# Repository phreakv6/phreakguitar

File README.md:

# PhreakGuitar

A guitar rig in your browser, built on circuit simulation. Plug in an audio
interface and play through amps and pedals whose analog circuits are solved
in real time: every resistor, capacitor, diode, transistor and tube, the same
netlists a SPICE simulator runs, checked against ngspice.

**Live:** https://phreakguitar.com

## What's in it

- **11 amps** as circuit models: tweed, black-panel, British plexi and
  master-volume, class A, high-headroom, graphic-panel, boutique overdrive
  (plus an experimental hot-rod high-gain head). Each has its own power
  section with a simulated power supply that sags and recovers, a Response
  knob, and a glowing tube view.
- **12 pedals**: wah, clean and treble boosters, silicon and germanium
  round fuzz, octave fuzz, two overdrives, a distortion, a four-stage
  phaser (with its LFO in the circuit), a photocell vibe (a measured DSP
  model, the one pedal that isn't a solved circuit) and a four-stage
  fuzz; plus a compressor, 7-band EQ, digital delay, reverb and a looper.
- **Song tones and factory presets**, level-matched, with notes on how to
  play them; save, compare (A/B), export and import your own.
- **Pedal designer**: fork any pedal, swap parts and models, add parts on the
  schematic, probe any point with a live scope, hear each change as you play.
- **Tabs beside the rig**: open Guitar Pro or MusicXML files, play along
  with a cursor, slow it down, loop a section, mute your part.
- **Stage view**, keyboard shortcuts, a tuner, cab IRs (built-in or your
  own WAV files), and a latency readout with a loopback measurement.

## Using it

- Use an audio interface and headphones or speakers. A laptop's built-in
  microphone and speakers will feed back.
- Chrome or Edge on a desktop is best (they let you pick the output
  device). Safari and Firefox mostly work.
- Your audio never leaves your computer: everything runs in the browser, and
  presets, IRs and tabs are stored in it. The public site counts anonymous
  usage (page views, power on/off, which amps, pedals and presets get picked)
  with PostHog: no cookies, no recordings, no file names. Add `?notrack` to
  the address to opt out; builds you run yourself send nothing.
- Add `?rename` to the address to give the amps and pedals your own names
  (a Rename button by the amp and on the open pedal circuit). They're kept
  in your browser only; a blank name restores the built-in one.

## Running it locally

You need [Node.js](https://nodejs.org) 20+ and
[Emscripten](https://emscripten.org/docs/getting_started/downloads.html)
(installed to `~/emsdk`, or with `em++` on your `PATH`).

```sh
cd web
npm install
npm run dev        # builds the engine to WebAssembly, then serves the app
```

Open the printed URL (http://localhost:5173). The dev server also lists
cab IRs from `~/Music/PhreakGuitar/IRs` and tab files from
`~/Music/PhreakGuitar/Tabs` and `~/Downloads`.

The native build (unit tests, the offline render tool, a JUCE plugin) uses
CMake 3.24+ and a C++20 compiler; it fetches JUCE and Catch2:

```sh
cmake -B build -DCMAKE_BUILD_TYPE=Release
cmake --build build --config Release
ctest --test-dir build -C Release
tools/run_checks.sh   # the full suite; circuit checks need ngspice
```

## How it works

See [docs/ARCHITECTURE.md](docs/ARCHITECTURE.md): the nodal DK-method
solver, circuits as SPICE files, amps and power supplies, the browser
engine. What's next: [docs/ROADMAP.md](docs/ROADMAP.md).

## License

GPLv3, see [LICENSE](LICENSE). Third-party components and their licenses:
[THIRD_PARTY_NOTICES.md](THIRD_PARTY_NOTICES.md).

Amp and pedal models are named for the kind of gear they are, and each says
which original it's based on. Those product names (in the app and in source
comments) are trademarks of their owners, used only to identify the circuits
a model studies. PhreakGuitar is
not affiliated with or endorsed by any manufacturer.

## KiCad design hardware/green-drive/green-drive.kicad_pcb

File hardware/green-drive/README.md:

# Green Drive: the real pedal

The '808-style overdrive from `pedals/green-drive.cir`, as a board you can
order, solder and put in a 3D-printed box. The board's audio circuit is the
one the app plays, part for part: `check.py` compares KiCad's netlist with the
`.cir` on every build.

## What's here

| File | What it is |
|---|---|
| `out/green-drive-gerbers.zip` | **Upload this to Lion Circuits.** 2 layers, 64 x 66 mm |
| `out/assembly.pdf` | Soldering map: every part with its value, polarity marked |
| `out/bom.csv` | Parts list |
| `out/case_shell.stl`, `out/case_bottom.stl` | The box (print after measuring your parts, below) |
| `out/green-drive-schematic.pdf` | The schematic |
| `green-drive.kicad_pro` / `_sch` / `_pcb` | The KiCad project, if you want to change anything |
| `design.py` | Every part and what it connects to: the source of the rest |

## 1. Order the board

[lioncircuits.com](https://www.lioncircuits.com) → instant quote → upload
`out/green-drive-gerbers.zip`. Defaults are fine: 2 layers, FR-4 1.6 mm,
HASL, green mask, white legend, quantity 5. About ₹799, 5 to 6 days.

## 2. Buy the parts (Robu.in, checked 10 Nov 2026)

| Qty | Part | Value | On the board |
|---|---|---|---|
| 1 | Resistor 1/4 W metal film | 100 | R14 |
| 1 | Resistor 1/4 W metal film | 220 | R9 |
| 4 | Resistor 1/4 W metal film | 1k | R1, R7, R8, R10 |
| 1 | Resistor 1/4 W metal film | 2.2k | R21 |
| 1 | Resistor 1/4 W metal film | 4.7k | R6 |
| 7 | Resistor 1/4 W metal film | 10k | R3, R4, R13, R15, R16, R17, R18 |
| 1 | Resistor 1/4 W metal film | 15k | R20 |
| 1 | Resistor 1/4 W metal film | 51k | R5 |
| 1 | Resistor 1/4 W metal film | 510k | R2 |
| 2 | Resistor 1/4 W metal film | 1M | R12, R19 |
| 1 | Film capacitor | 22n | C1 |
| 1 | Film capacitor | 47n | C3 |
| 1 | Film capacitor | 100n | C7 |
| 2 | Film capacitor | 220n | C6, C10 |
| 1 | Ceramic capacitor | 47p | C11 |
| 1 | Ceramic capacitor | 100n | C13 |
| 2 | Electrolytic capacitor, 25 V+ | 1u | C2, C5 |
| 1 | Electrolytic capacitor, 25 V+ | 10u | C8 |
| 1 | Electrolytic capacitor, 25 V+ | 47u | C9 |
| 1 | Electrolytic capacitor, 25 V+ | 100u | C12 |
| 2 | Diode | 1N4148 | D1, D3 |
| 1 | Schottky diode | 1N5819 | D4 |
| 2 | NPN transistor | 2SC1815 | Q1, Q2 |
| 1 | Dual op-amp, DIP-8 | JRC4558D (also try RC4558P, TL072) | U1 |
| 1 | Pot, 16 mm, PCB legs | B500K (A500K if you find one) | RV1 Drive |
| 1 | Pot, 16 mm, PCB legs | B20K | RV2 Tone |
| 1 | Pot, 16 mm, PCB legs | B100K (A100K if you find one) | RV3 Level |
| 1 | LED, 5 mm | red | LED1 |
| 1 | 8-pin DIP socket | | U1 |
| 1 | 3PDT footswitch | Daier PBS-24-302P | |
| 2 | 1/4" jack | CK-6.35-03 (stereo is fine) | |
| 1 | DC jack, panel mount | 2.1 x 5.5 mm | |
| 3 | Knob, 6 mm shaft | | |
| 4 | M3 x 5 mm brass heat-set insert + M3 x 6 mm countersunk screw | | bottom plate |
| | 24 AWG wire, two colours | | |

Notes:
- The board takes film caps at **5 mm or 10 mm** lead spacing (three holes:
  use the pair that fits) and the 47p at 2.5 or 5 mm.
- **R20 (15k)** makes the linear Level pot feel like an audio-taper one. With
  an A100K pot, leave R20 out.
- C1 is 22n (the original's 20n is rare) and C11 47p (51p): both checked in
  ngspice, under 0.5 dB anywhere on the knobs.

## 3. Solder

Follow `out/assembly.pdf`. Low parts first, so the board lies flat while you
work:

1. Resistors, the three diodes (band = **K** on the map)
2. The DIP socket (notch at the **1** end), the 47p and 100n ceramics
3. The transistors: the **thick line on the map is the flat face**, legs E-C-B
4. Film caps, then electrolytics (long leg = **+**)
5. Wires to the pads: about 10 cm each, two colours for 9V and GND
6. **Last, on the other side of the board:** the pots and the LED. Push the
   pots' shafts through the printed lid first and screw the nuts on, then
   solder, so they line up with the holes. Push the LED until its tip sits in
   the lid's LED hole, then solder it. Break off the pots' little
   anti-rotation tabs with pliers.

Don't put the op-amp in yet.

## 4. Test before boxing

9 V adapter on the 9V and GND pads, multimeter on DC volts, black probe on
GND. Without the op-amp:

| Where | Expect |
|---|---|
| D4's band end (VCC) | 8.5 to 8.8 V (the diode takes 0.3 to 0.4 V) |
| C9's + leg (VREF) | half of that, about 4.3 V |

Then power off, put the op-amp in (notch to the **1** end), power on:

| Where | Expect (from ngspice, scaled to the real supply) |
|---|---|
| U1 pins 1, 2, 3, 5, 6, 7 | all about VREF (4.3 V) |
| Q1 emitter (E) | about 3.1 V |
| Q2 emitter (E) | about 2.7 V |

The pedal should draw about 10 mA with the LED on. If it draws much more
than 20 mA, or a voltage is way off, power off
and look for a solder bridge or a part in backwards before going further.

## 5. Wire the jacks and footswitch

Check the footswitch with a multimeter on continuity first: its 9 lugs are
three columns of three. In each column the middle lug connects to the top lug
in one position and to the bottom lug in the other. Looking at the lugs:

```
 1  2  3     top row:    bypass
 4  5  6     middle row: commons
 7  8  9     bottom row: effect on
```

| From | To |
|---|---|
| Lug 4 | Output jack tip |
| Lug 5 | Input jack tip |
| Lug 6 | GND |
| Lug 1 | Lug 2 (a short jumper: the bypass path) |
| Lug 7 | Board **OUT** pad |
| Lug 8 | Board **IN** pad |
| Lug 9 | Board **LED-** pad |
| Both jack sleeves | Board **GND** pad (the one next to IN) |
| DC jack centre pin | Board **GND** pad (the one next to 9V) |
| DC jack sleeve | Board **9V** pad |

Use the stereo jacks' tip and sleeve only; leave the ring lug empty. Find the
DC jack's centre-pin lug with the multimeter. Pedal adapters are centre
negative; if one is wired backwards, D4 blocks it and nothing is harmed.

If the LED lights when the pedal is bypassed, the rows are the other way up
on your switch: swap the top-row and bottom-row wires.

## 6. The box

`out/case_shell.stl` (print it lid-down: no supports, flat face) and
`out/case_bottom.stl`. PETG or PLA, 4 walls, 40% infill.

**Before printing, measure your parts** and set the values marked MEASURE in
`enclosure.py`, then run `python3 enclosure.py`:
- the pot bushing, jack and DC jack threads (hole sizes)
- `POT_SHAFT_OFFSET_MEASURED`: shaft centre to the row of pins on your pots
  (the board assumes 7.5 mm). Only the lid's holes move; the board stays as
  ordered.

Press the M3 inserts into the four corner posts with a soldering iron. The
input jack goes on the right side as you look at the knobs, output and DC
jack on the left.

## 7. Rebuilding after a change

```
python3 build.py      # schematic, netlist, ERC, check against the .cir
KPY=/Applications/KiCad/KiCad.app/Contents/Frameworks/Python.framework/Versions/3.9/bin/python3.9
$KPY pcb.py           # place the parts
$KPY route.py path/to/freerouting.jar   # route (Freerouting 2.5, needs Java)
kicad-cli pcb drc --schematic-parity --refill-zones green-drive.kicad_pcb
python3 assembly.py && python3 bom.py && python3 enclosure.py
./fab.sh              # Gerbers + drill -> out/green-drive-gerbers.zip
```
Freerouting is at github.com/freerouting/freerouting/releases.

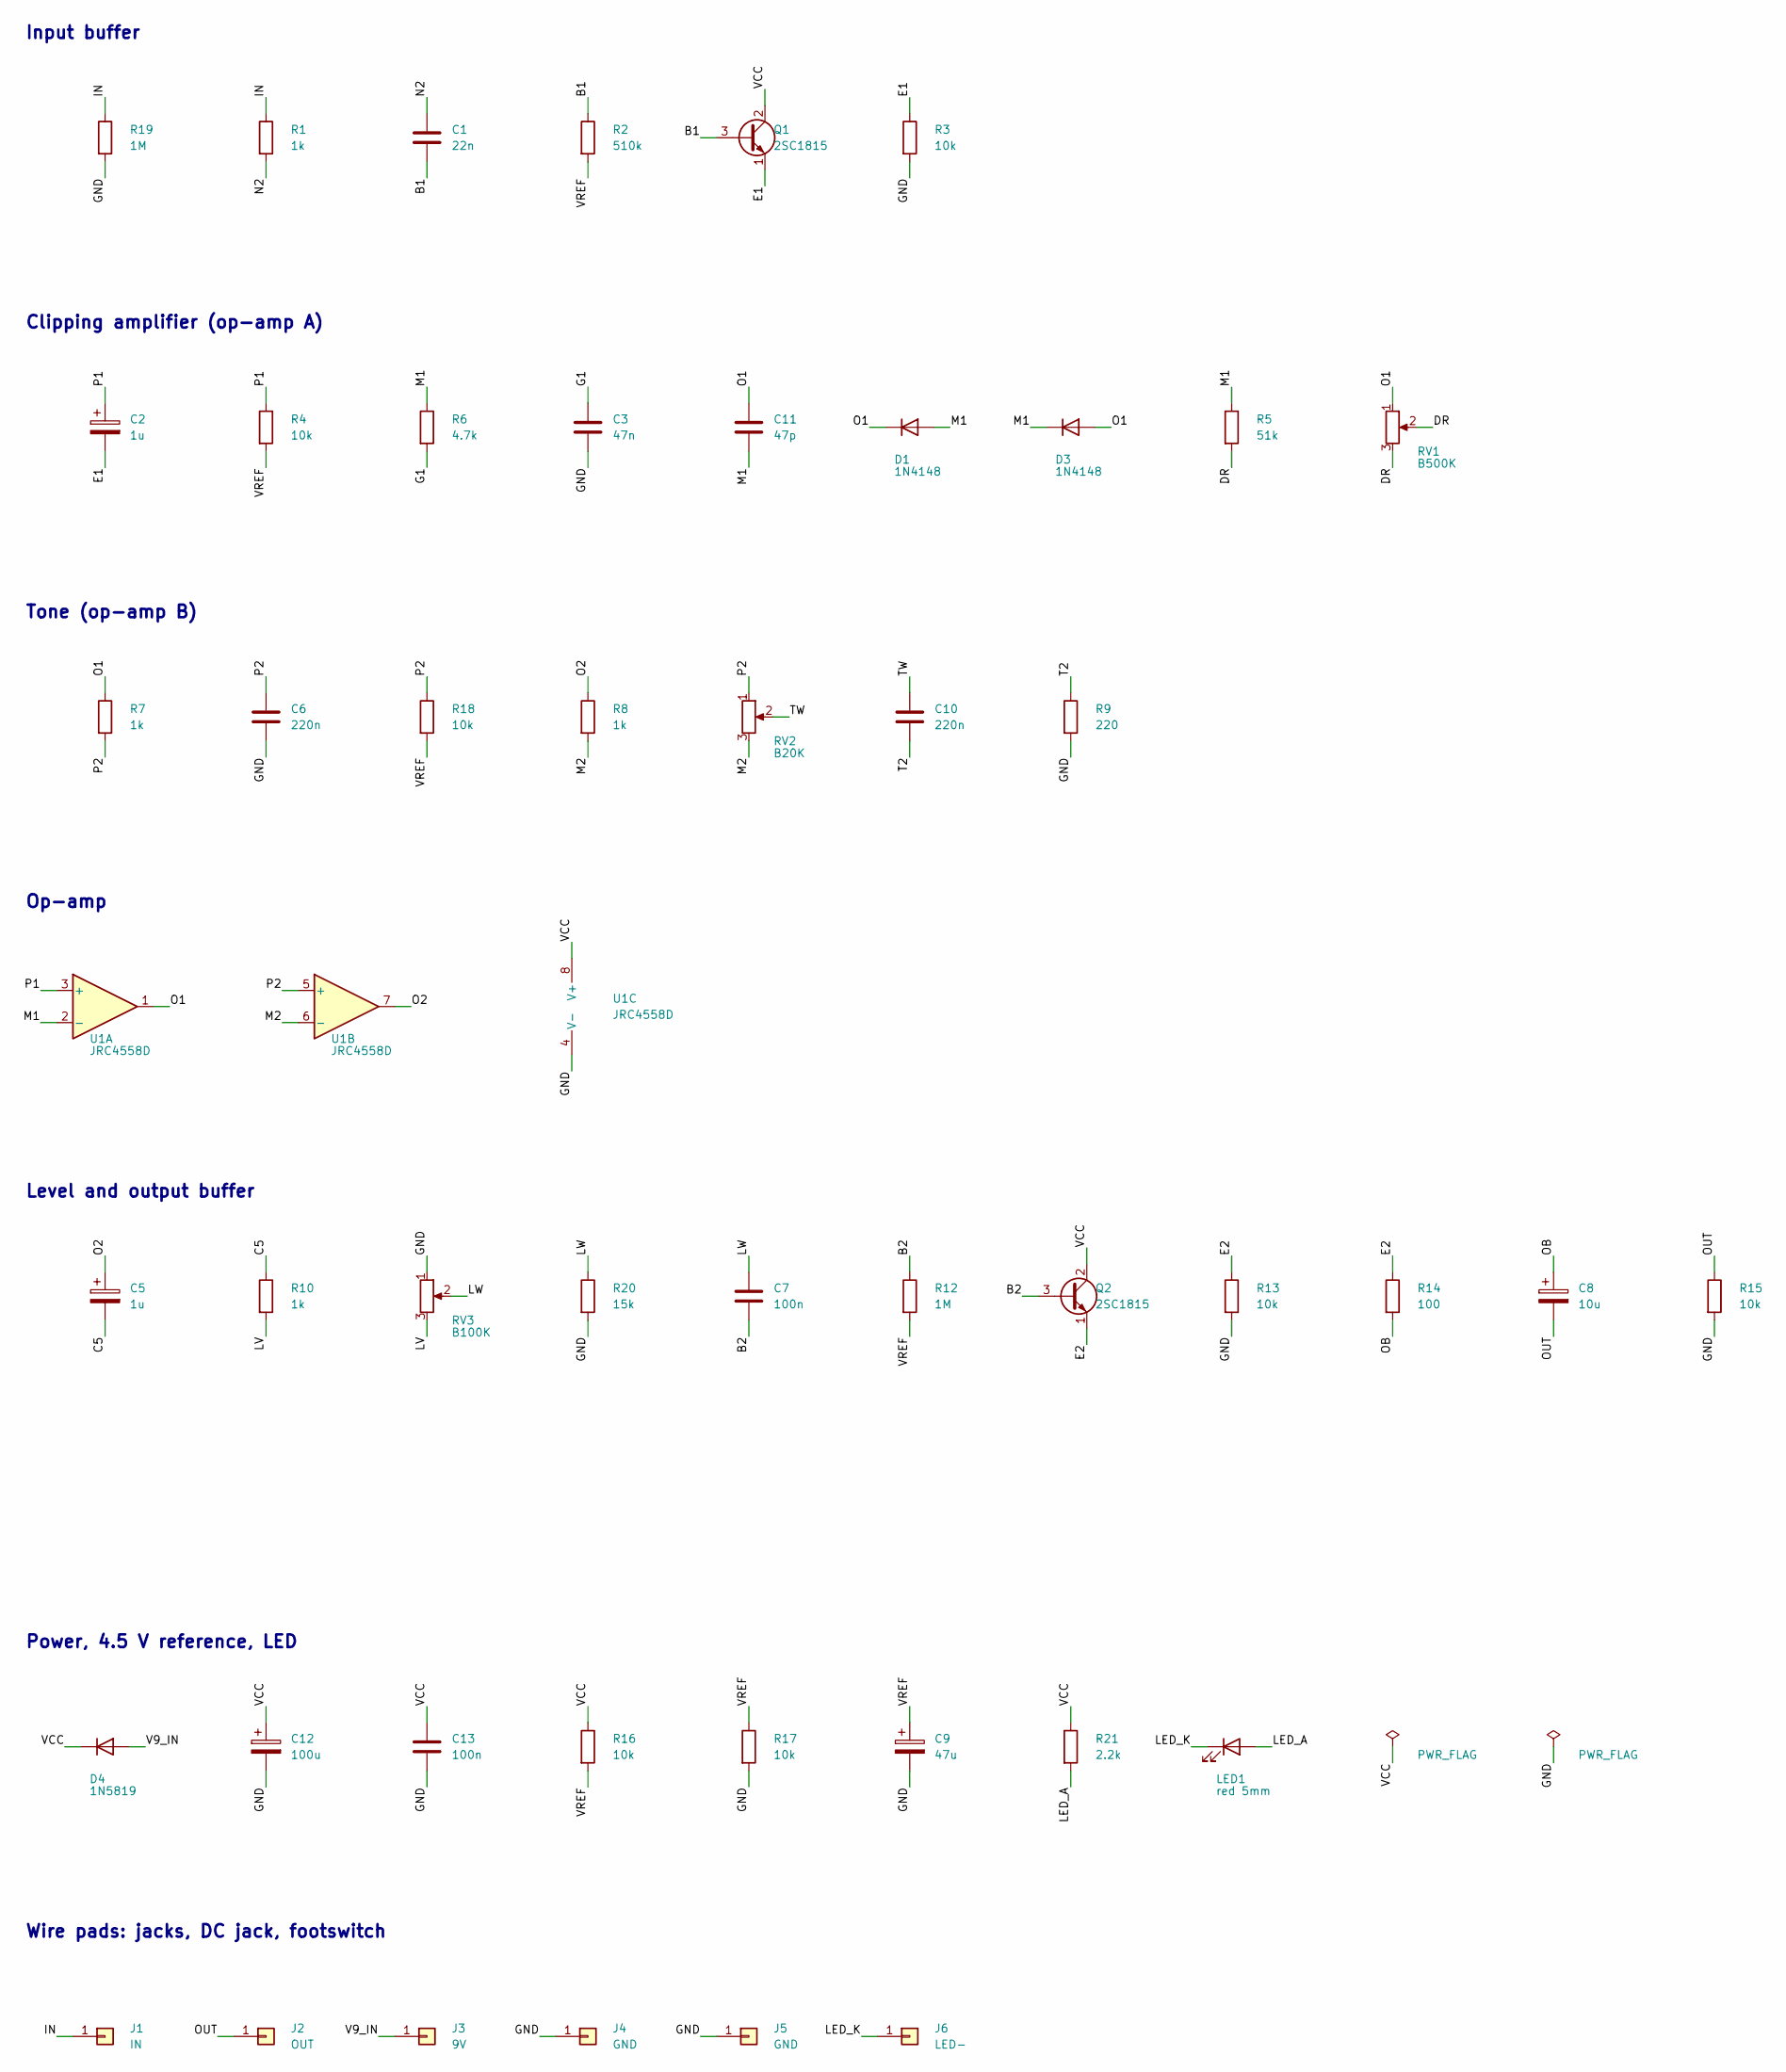
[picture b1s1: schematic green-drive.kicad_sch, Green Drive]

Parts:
C1: 22n; C_Film_P5_P10
C2, C5: 1u; CP_Radial_D5.0mm_P2.00mm
C3: 47n; C_Film_P5_P10
C6, C10: 220n; C_Film_P5_P10
C7: 100n; C_Film_P5_P10
C8: 10u; CP_Radial_D5.0mm_P2.00mm
C9: 47u; CP_Radial_D5.0mm_P2.00mm
C11: 47p; C_Disc_P2.5_P5
C12: 100u; CP_Radial_D6.3mm_P2.50mm
C13: 100n; C_Disc_P2.5_P5
D1, D3: 1N4148; D_DO-35_SOD27_P7.62mm_Horizontal
D4: 1N5819; D_DO-41_SOD81_P10.16mm_Horizontal
J1: IN; SolderWire-0.5sqmm_1x01_D0.9mm_OD2.1mm
J2: OUT; SolderWire-0.5sqmm_1x01_D0.9mm_OD2.1mm
J3: 9V; SolderWire-0.5sqmm_1x01_D0.9mm_OD2.1mm
J4, J5: GND; SolderWire-0.5sqmm_1x01_D0.9mm_OD2.1mm
J6: LED-; SolderWire-0.5sqmm_1x01_D0.9mm_OD2.1mm
LED1: red 5mm; LED_D5.0mm
Q1, Q2: 2SC1815; TO-92_Inline
R1, R7, R8, R10: 1k; R_Axial_DIN0207_L6.3mm_D2.5mm_P7.62mm_Horizontal
R2: 510k; R_Axial_DIN0207_L6.3mm_D2.5mm_P7.62mm_Horizontal
R3, R4, R13, R15, R16, R17, R18: 10k; R_Axial_DIN0207_L6.3mm_D2.5mm_P7.62mm_Horizontal
R5: 51k; R_Axial_DIN0207_L6.3mm_D2.5mm_P7.62mm_Horizontal
R6: 4.7k; R_Axial_DIN0207_L6.3mm_D2.5mm_P7.62mm_Horizontal
R9: 220; R_Axial_DIN0207_L6.3mm_D2.5mm_P7.62mm_Horizontal
R12, R19: 1M; R_Axial_DIN0207_L6.3mm_D2.5mm_P7.62mm_Horizontal
R14: 100; R_Axial_DIN0207_L6.3mm_D2.5mm_P7.62mm_Horizontal
R20: 15k; R_Axial_DIN0207_L6.3mm_D2.5mm_P7.62mm_Horizontal
R21: 2.2k; R_Axial_DIN0207_L6.3mm_D2.5mm_P7.62mm_Horizontal
RV1: B500K; Pot_WH148_16mm
RV2: B20K; Pot_WH148_16mm
RV3: B100K; Pot_WH148_16mm
U1: JRC4558D; DIP-8_W7.62mm_Socket

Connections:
/B1: C1.2, Q1.3 (B), R2.1
/B2: C7.2, Q2.3 (B), R12.1
/C5: C5.2, R10.1
/DR: R5.2, RV1.2, RV1.3
/E1: C2.2, Q1.1 (E), R3.1
/E2: Q2.1 (E), R13.1, R14.1
/G1: C3.1, R6.2
/GND: C3.2, C6.2, C9.2, C12.2, C13.2, J4.1, J5.1, R3.2, R9.2, R13.2, R15.2, R17.2, R19.2, R20.2, RV3.1, U1.4 (V-)
/IN: J1.1, R1.1, R19.1
/LED_A: LED1.2 (A), R21.2
/LED_K: J6.1, LED1.1 (K)
/LV: R10.2, RV3.3
/LW: C7.1, R20.1, RV3.2
/M1: C11.2, D1.2 (A), D3.1 (K), R5.1, R6.1, U1.2 (-)
/M2: R8.2, RV2.3, U1.6 (-)
/N2: C1.1, R1.2
/O1: C11.1, D1.1 (K), D3.2 (A), R7.1, RV1.1, U1.1
/O2: C5.1, R8.1, U1.7
/OB: C8.1, R14.2
/OUT: C8.2, J2.1, R15.1
/P1: C2.1, R4.1, U1.3 (+)
/P2: C6.1, R7.2, R18.1, RV2.1, U1.5 (+)
/T2: C10.2, R9.1
/TW: C10.1, RV2.2
/V9_IN: D4.2 (A), J3.1
/VCC: C12.1, C13.1, D4.1 (K), Q1.2 (C), Q2.2 (C), R16.1, R21.1, U1.8 (V+)
/VREF: C9.1, R2.2, R4.2, R12.2, R16.2, R17.1, R18.2

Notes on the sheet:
Input buffer
Clipping amplifier (op-amp A)
Tone (op-amp B)
Op-amp
Level and output buffer
Power, 4.5 V reference, LED
Wire pads: jacks, DC jack, footswitch

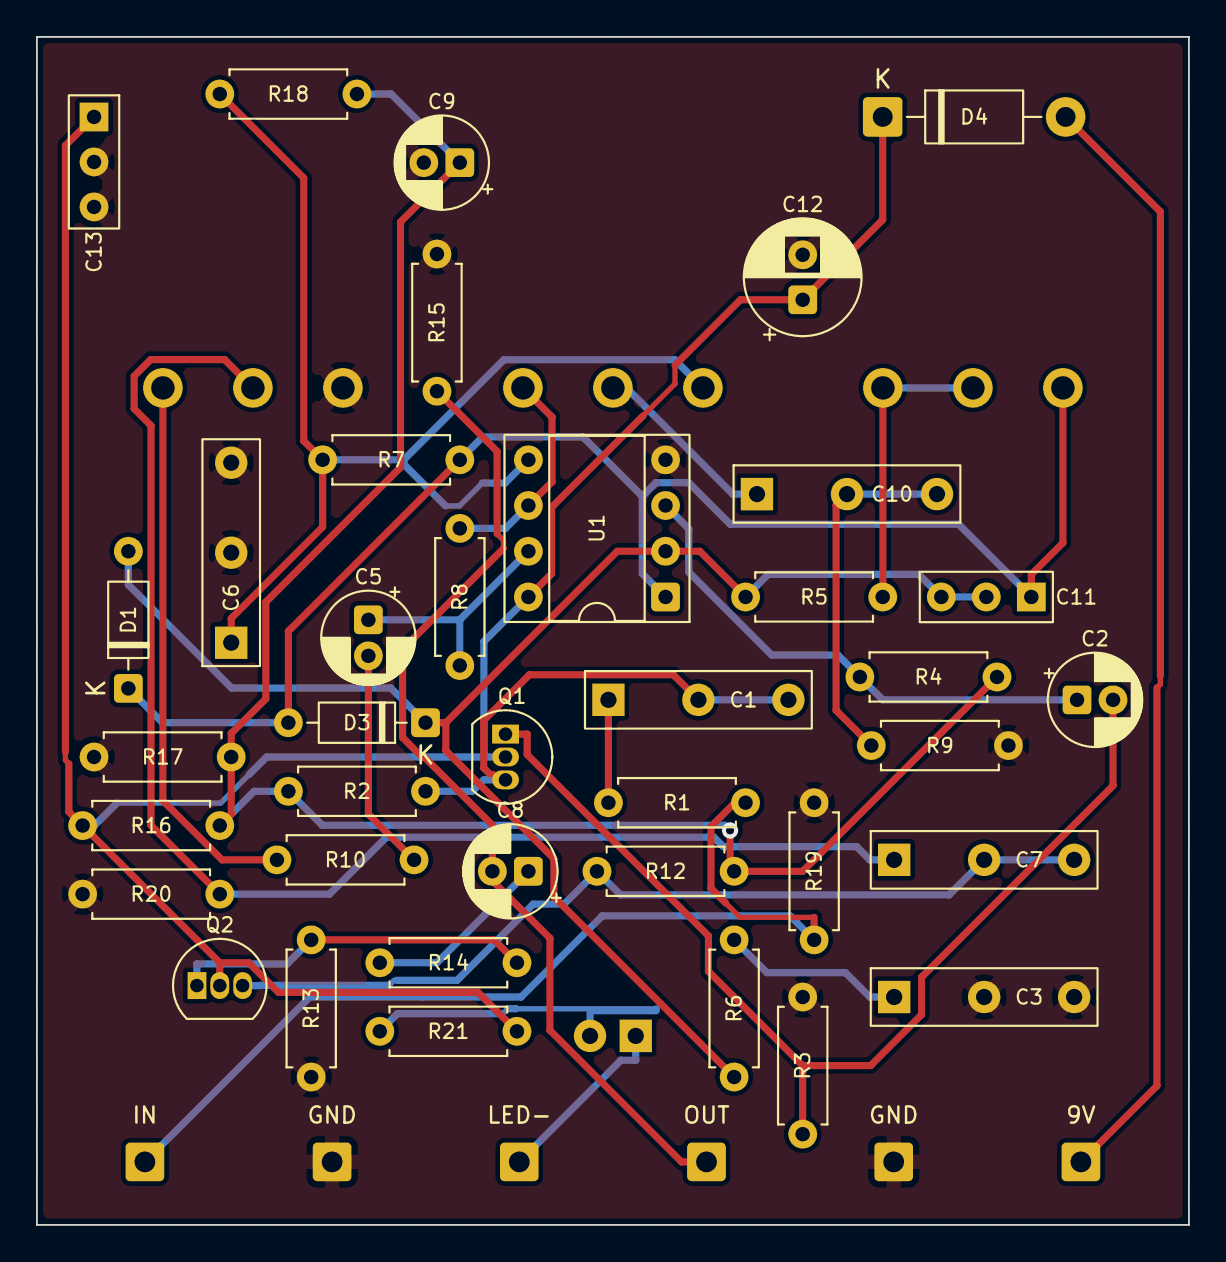
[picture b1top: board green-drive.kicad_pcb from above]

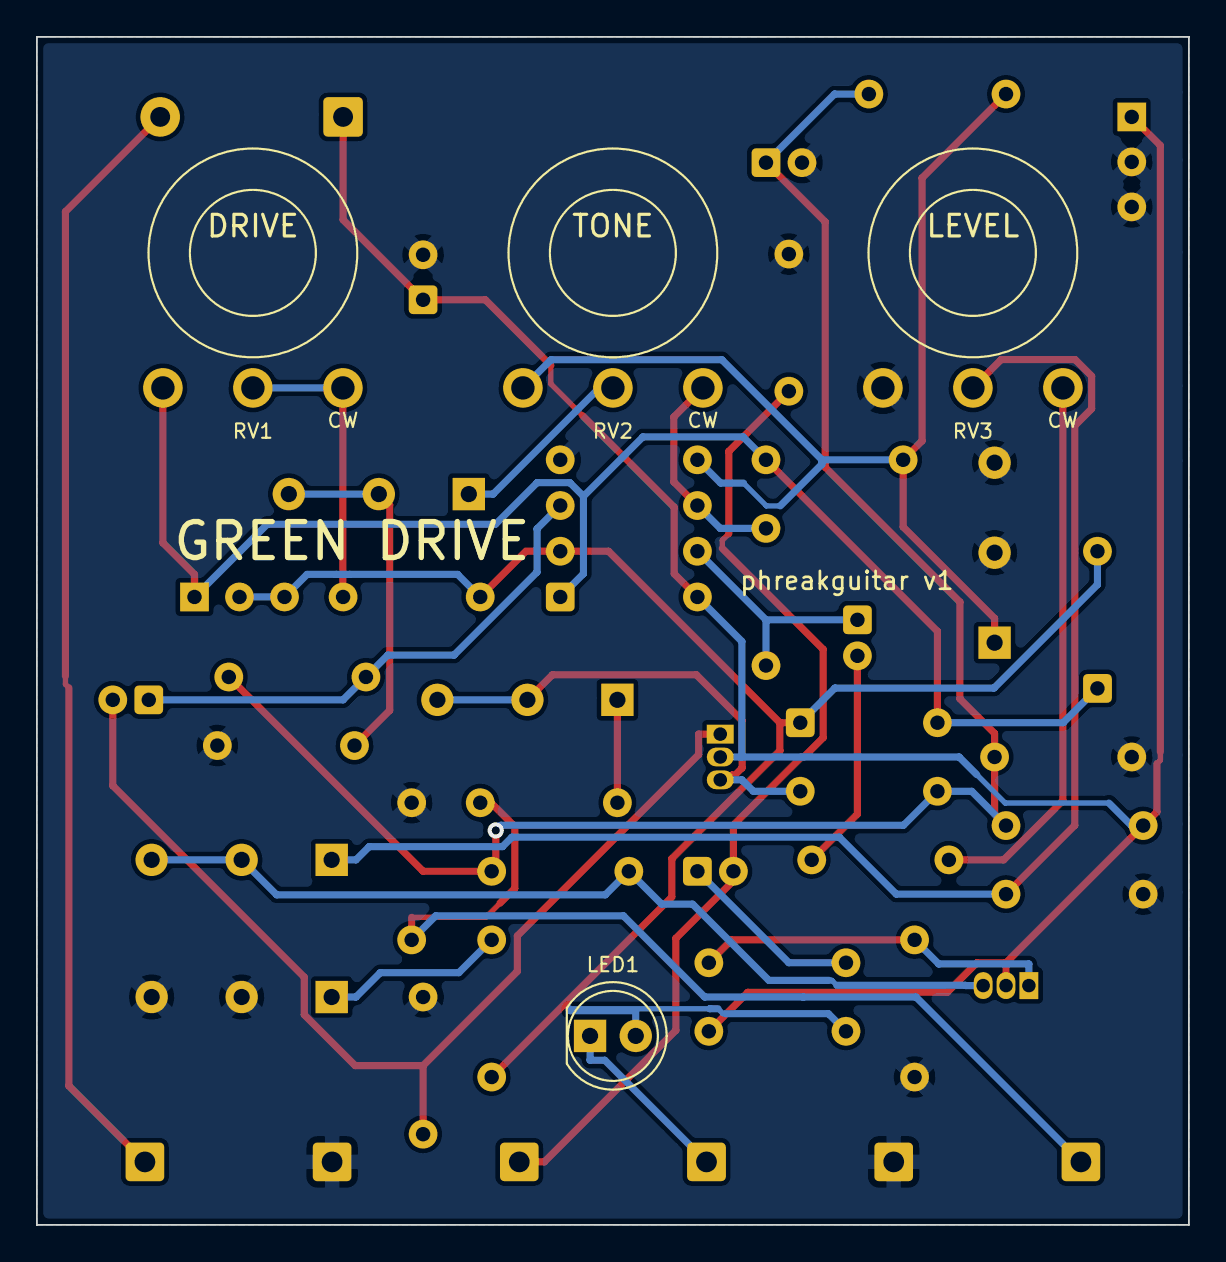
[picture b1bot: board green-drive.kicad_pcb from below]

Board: 2 copper layers, 64.0 x 66.0 mm, 48 parts (4 on the bottom side), 27 nets.

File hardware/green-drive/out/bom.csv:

Qty,Part,Value,References,Notes
1,Resistor 1/4 W metal film,100,R14,
1,Resistor 1/4 W metal film,220,R9,
4,Resistor 1/4 W metal film,1k,"R1, R7, R8, R10",
1,Resistor 1/4 W metal film,2.2k,R21,
1,Resistor 1/4 W metal film,4.7k,R6,
7,Resistor 1/4 W metal film,10k,"R3, R4, R18, R13, R15, R16, R17",
1,Resistor 1/4 W metal film,15k,R20,only with a linear Level pot
1,Resistor 1/4 W metal film,51k,R5,
1,Resistor 1/4 W metal film,510k,R2,
2,Resistor 1/4 W metal film,1M,"R19, R12",pull-down (not in the .cir)
1,Film capacitor (polyester box),22n,C1,.cir: 20n
1,Film capacitor (polyester box),47n,C3,
1,Film capacitor (polyester box),100n,C7,
2,Film capacitor (polyester box),220n,"C6, C10",
1,Ceramic capacitor,47p,C11,.cir: 51p
1,Ceramic capacitor,100n,C13,
2,"Electrolytic capacitor, 25 V+",1u,"C2, C5",
1,"Electrolytic capacitor, 25 V+",10u,C8,
1,"Electrolytic capacitor, 25 V+",47u,C9,
1,"Electrolytic capacitor, 25 V+",100u,C12,
2,Diode,1N4148,"D1, D3",
1,Schottky diode,1N5819,D4,reverse-polarity protection
2,NPN transistor (pins E-C-B),2SC1815,"Q1, Q2",
1,"Dual op-amp, DIP-8",JRC4558D,U1,or RC4558P / TL072
1,"Pot, 16 mm, PCB legs",B20K,RV2,
1,"Pot, 16 mm, PCB legs",B100K,RV3,A100K if you find one
1,"Pot, 16 mm, PCB legs",B500K,RV1,A500K if you find one
1,LED,red 5mm,LED1,
1,8-pin DIP socket,,,for U1
1,3PDT footswitch (Daier PBS-24-302P),,,true bypass + LED
2,"1/4"" jack (CK-6.35-03, stereo is fine)",,,input and output
1,"2.1 x 5.5 mm DC jack, panel mount",,,"centre negative, like Boss"
3,"Knob, 6 mm shaft",,,
1,24 AWG hook-up wire,,,a couple of colours
4,M3 x 5 mm brass heat-set insert,,,bottom plate
4,M3 x 6 mm countersunk screw,,,bottom plate
